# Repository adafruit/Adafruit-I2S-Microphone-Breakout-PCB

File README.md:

## Adafruit I2S Microphone Breakout PCB

<a href="http://www.adafruit.com/products/3421"><br/>
Click here to purchase one from the Adafruit shop</a>

PCB files for the Adafruit I2S Microphone Breakout. Format is EagleCAD schematic and board layout
* https://www.adafruit.com/products/3421

### Description

Listen to this good news - we now have a breakout board for a super tiny I2S MEMS microphone. Just like 'classic' electret microphones, MEMS mics can detect sound and convert it to voltage, but they're way smaller and thinner. This microphone doesn't even have analog out, its purely digital. The I2S is a small, low cost MEMS mic with a range of about 50Hz - 15KHz, good for just about all general audio recording/detection.

For many microcontrollers, adding audio input is easy with one of our analog microphone breakouts. But as you get to bigger and better microcontrollers and microcomputers, you'll find that you don't always have an analog input, or maybe you want to avoid the noise that can seep in with an analog mic system. Once you get past 8-bit micros, you will often find an I2S peripheral, that can take digital audio data in! That's where this I2S Microphone Breakout comes in.

Instead of an analog output, there are three digital pins: Clock, Data and Left-Right (Word Select) Clock. When connected to your microcontroller/computer, the 'I2S Master' will drive the clock and word-select pins at a high frequency and read out the data from the microphone. No analog conversion required!

The microphone is a single mono element. You can select whether you want it to be on the Left or Right channel by connecting the Select pin to power or ground. If you need stereo, pick up two microphones! You can set them up to be stereo by sharing the Clock, WS and Data lines but having one with Select to ground, and one with Select to high voltage.

This I2S MEMS microphone is bottom ported, so make sure you have the hole in the bottom facing out towards the sounds you want to read. It's a 1.6-3.6V max device only, so not for use with 5V logic (its really unlikely you'd have a 5V-logic device with I2S anyways). Many beginner microcontroller boards don't have I2S, so make sure its a supported interface before you try to wire it up! This microphone is best used with Cortex M-series chips like the Arduino Zero, Feather M0, or single-board computers like the Raspberry Pi.

### License

Adafruit invests time and resources providing this open source design, please support Adafruit and open-source hardware by purchasing products from [Adafruit](https://www.adafruit.com)!

Designed by Limor Fried/Ladyada for Adafruit Industries.

Creative Commons Attribution/Share-Alike, all text above must be included in any redistribution. See license.txt for additional details.

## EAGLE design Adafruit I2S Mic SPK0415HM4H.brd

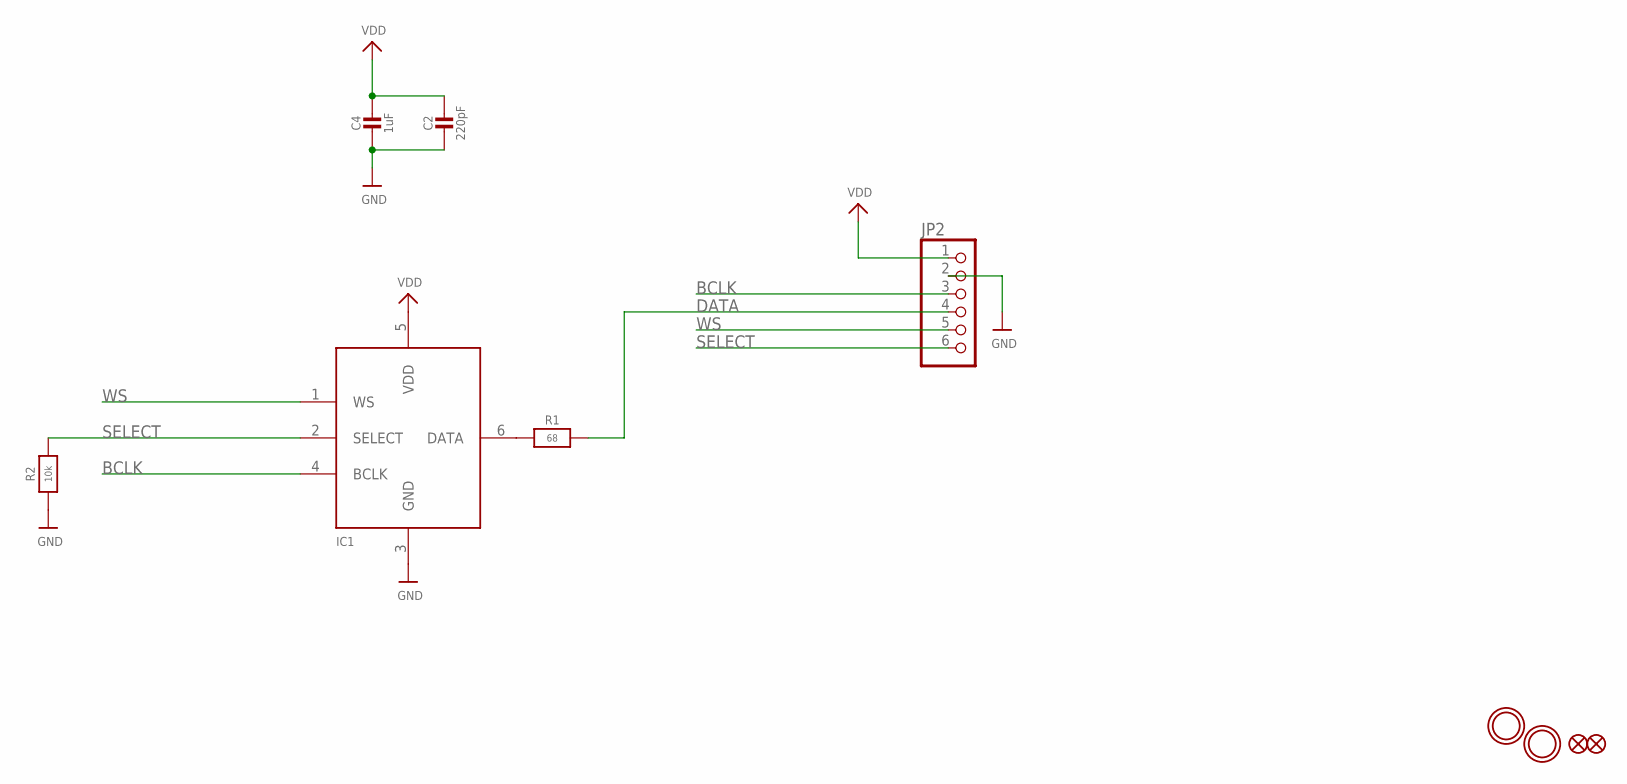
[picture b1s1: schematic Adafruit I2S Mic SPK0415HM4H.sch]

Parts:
C2: 220pF; 0805-NO
C4: 1uF; 0805-NO
FID1, FID2: FIDUCIAL_1MM
IC1: MIC_I2S_SPH0645; SPH0645LM4H
JP2: HEADER-1X6ROUND; 1X06_ROUND
R1: 68; 0603-NO
R2: 10k; 0603-NO
U$6, U$12: MOUNTINGHOLE2.5; MOUNTINGHOLE_2.5_PLATED

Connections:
BCLK: IC1.4 (BCLK), JP2.3
DATA: JP2.4, R1.2
GND: C2.2, C4.2, IC1.3 (GND), JP2.2, R2.1
unnamed: IC1.6 (DATA), R1.1
SELECT: IC1.2 (SELECT), JP2.6, R2.2
VDD: C2.1, C4.1, IC1.5 (VDD), JP2.1
WS: IC1.1 (WS), JP2.5

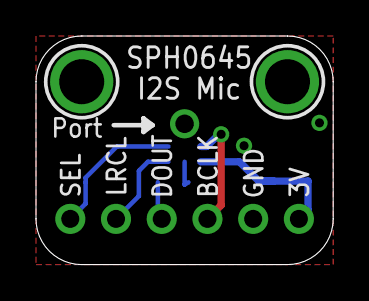
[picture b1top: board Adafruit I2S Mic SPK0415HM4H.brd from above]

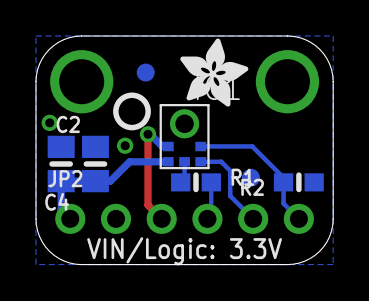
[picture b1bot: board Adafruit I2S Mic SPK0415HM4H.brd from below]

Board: 2 copper layers, 16.5 x 12.7 mm, 12 parts (10 on the bottom side), 7 nets.

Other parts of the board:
U$5: ADAFRUIT_3.5MM
U$13: PCBFEAT-REV-040

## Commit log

2017-02-22 init

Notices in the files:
parts and their libraries:
microbuilder: This work is placed in the public domain, and may be freely used for commercial and non-commercial work with the following conditions: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
